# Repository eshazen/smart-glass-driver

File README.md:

# smart-glass-driver

This is a line-powered programmable function generator capable
of generating an output of about 140V pk-pk on each of two outputs
(which can be out of phase).

Here are the specs from Darren:

1.  Provide amplitude up to about 60-70Vpp AC (note: not 60 VAC RMS),
    we need to be able to change the amplitude for testing, with
    likely voltages 20, 30, 40, 50, 60 VppAC
2.  We also need to be able to alter the AC frequency, from low Hz to
    up to at least 1 kHz.
3.  We need to be able to have control over the output, with the
    ability to modulate (binary turn on and off) the output signal
    from a few Hz to up to about 300Hz. We would use this for
    lock-in. I envision control with a digital I/O pin.

For 1kHz sine wave with ~16 samples per cycle, the sampling rate would
be 62.5us or for 8 samples 125us.  

We need to stop Timer0 to avoid the interrupts.  Use TimerOne library
to interrupt at 62us and take values from a table.  This seems to
work just fine.  **But** we need to do two channels
out of phase on two DACs.  Simulate this with Set1 and Set2 functions.

The slew rate of the LTC6090 is spec'd at 21V/us.  So for 120V this
would be about 6uS or a minimum cycle time of 12uS 80kHz so no problem
reproducing a 1kHz output.  This is well matched to the 5us slew of
the DAC.

## 2026-04-02

ECOs for "Eric's" board:

*  Solder a wire between pins 1 and 6 of U1 (best done on the bottom side)
This connects DAC reference to 5V
*  Solder a wire between J4 pin 3 and J2 pin 5
*  Solder a wire between J4 pin 4 and J2 pin 7.
This connects the SPI data and clock to the right Arduino pins

## 2026-04-01

Ordered parts to assemble a system based on a transformer-based zener supply
and two InTENS shield boards.

Investigating the MCP492x DAC using the BE511 shield board.
<br>DAC setting code for first test:

```
    // Write a word to DAC channel 0 only
    // Unbuffered mode so no need to manipulate LDAC
    void MCP4922::Set1( int A) {
      int channelA = A | 0b0011000000000000; // unbuffered mode, gain = 2X
      SPI.beginTransaction(SPISettings(MCP_CLOCK, MSBFIRST, SPI_MODE0));
      digitalWrite(_CS, LOW);
      SPI.transfer(highByte(channelA));
      SPI.transfer(lowByte(channelA));
      digitalWrite(_CS, HIGH);
      SPI.endTransaction();
    }
```

On an Uno R3 with SPI clk set to 8MHz this takes 17us (plus any timer
interrupt delay).  Also the DAC takes 5us to slew full scale (roughly
linear).

**Software Written**: sketch `DAC_Function_Gen` accepts integer rates
from 25-2000 Hz (more or less, up to 1kHz best).  Serial at 9600.

## 2026-03-31

### Testing the commercial setup

Made some measurements of the commercial driver with Weizhe.
General observations:

* Drive electronics supplied provides about 200V pk-pk AC
two-phase at 60Hz.  Not quite sinusoidal.
* Tested with 4.7k resistor in series.  Current waveform
is roughly in phase with voltage.  Amplitude is about 2mA (absolute value).

### Testing Amazon HV supply

Now testing an HV supply I found in the box with the InTENS stuff.

It claims to deliver up to 40W or 15mA.  

* Test with 47k load.  Get a pretty nasty ripple of 20V @ 10Hz.
* Test with 22k load.  Just as bad.

Probably not worth considering using this thing.

### Considering home-made supply

We could build a nice +/-65V supply using a Triad N-68X transformer,
bridge rectifier and an RC filter with zener regulator.

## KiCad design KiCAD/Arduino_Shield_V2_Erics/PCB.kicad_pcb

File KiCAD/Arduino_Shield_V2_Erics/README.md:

This is the "as built" shield design from InTENS.
(boards with blue soldermask).

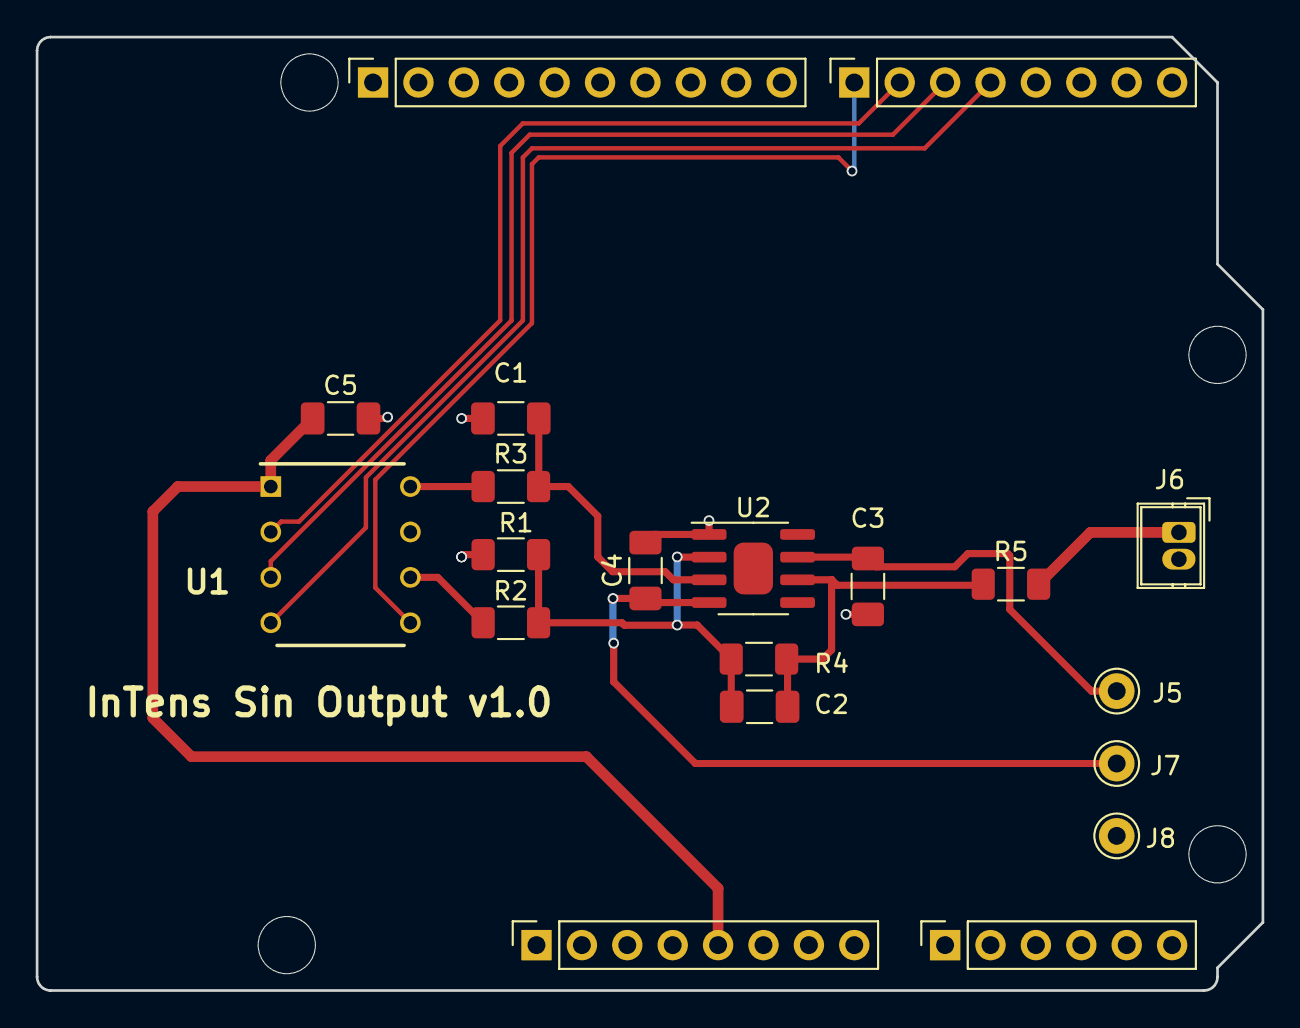
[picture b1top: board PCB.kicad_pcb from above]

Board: 2 copper layers, 68.6 x 53.3 mm, 24 parts (0 on the bottom side), 17 nets.

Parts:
C1: 470pF; C_1206_3216Metric_Pad1.33x1.80mm_HandSolder
C2: 10pF; C_1206_3216Metric_Pad1.33x1.80mm_HandSolder
C3, C4: 0.1uF; C_1206_3216Metric_Pad1.33x1.80mm_HandSolder
C5: 0.1 uF; C_1206_3216Metric_Pad1.33x1.80mm_HandSolder
J1: Power; PinSocket_1x08_P2.54mm_Vertical
J2: Digital/PWM; PinSocket_1x10_P2.54mm_Vertical
J3: Analog; PinSocket_1x06_P2.54mm_Vertical
J4: Digital/PWM; PinSocket_1x08_P2.54mm_Vertical
J5, J7, J8: Conn_01x01; Pin_D1.0mm_L10.0mm
J6: Conn_01x01_Socket; Wuerth_WR-WTB_64800211622_1x02_P1.50mm_Vertical
MH1, MH2, MH3, MH4: MountingHole_3.2mm
R1: 16.2kΩ; R_1206_3216Metric_Pad1.30x1.75mm_HandSolder
R2: 16.9kΩ; R_1206_3216Metric_Pad1.30x1.75mm_HandSolder
R3: 10kΩ; R_1206_3216Metric_Pad1.30x1.75mm_HandSolder
R4: 453kΩ; R_1206_3216Metric_Pad1.30x1.75mm_HandSolder
R5: 40kΩ; R_1206_3216Metric_Pad1.30x1.75mm_HandSolder
U1: MCP4921; DIP781W56P254L950H533Q8N
U2: LTC6090; SOIC-8-1EP_3.9x4.9mm_P1.27mm_EP2.29x3mm

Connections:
+5V: C5.1, J1.5, U1.1 (Vdd)
-VSW: C4.1, J7.1, U2.4
/4: J4.4, U1.4 (SDI)
/7: J4.1, U1.5 (~LDAC)
/*5: J4.3, U1.3 (SCK)
/*6: J4.2, U1.2 (~CS)
/HV_OA: C2.2, R4.2, R5.1, U2.6
/HV_OUT: J6.1, R5.2
/SCL/A5: J2.1, J3.6
/SDA/A4: J2.2, J3.5
GND: C1.2, C3.2, C4.2, C5.2, J1.6, J1.7, J2.4, J6.2, J8.1, R2.1, U1.7 (Vss), U2.1
HT: C3.1, J5.1, U2.7
unnamed: C1.1, R3.2, U2.3
unnamed: C2.1, R1.1, R2.2, R4.1, U2.2
unnamed: R3.1, U1.8 (Vout)
unnamed: R1.2, U1.6 (Vref)
unnamed: U2.5, U2.8

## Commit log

2026-03-25 starting on schematic
2026-04-01 initial software
2026-04-02 Readme
2026-04-16 box and wiring
2026-04-22 update box, wiring
2026-04-23 DAC_Function_Gen working on one board
2026-04-28 Add amplitude and phase to cli
2026-04-30 update DIY drawing
2026-04-30 Update documentation
2026-04-30 Schematic notes; initial software working
2026-05-01 Add files via upload
    Updated DAC code with gate (on/off) frequency control, and a turning off function
